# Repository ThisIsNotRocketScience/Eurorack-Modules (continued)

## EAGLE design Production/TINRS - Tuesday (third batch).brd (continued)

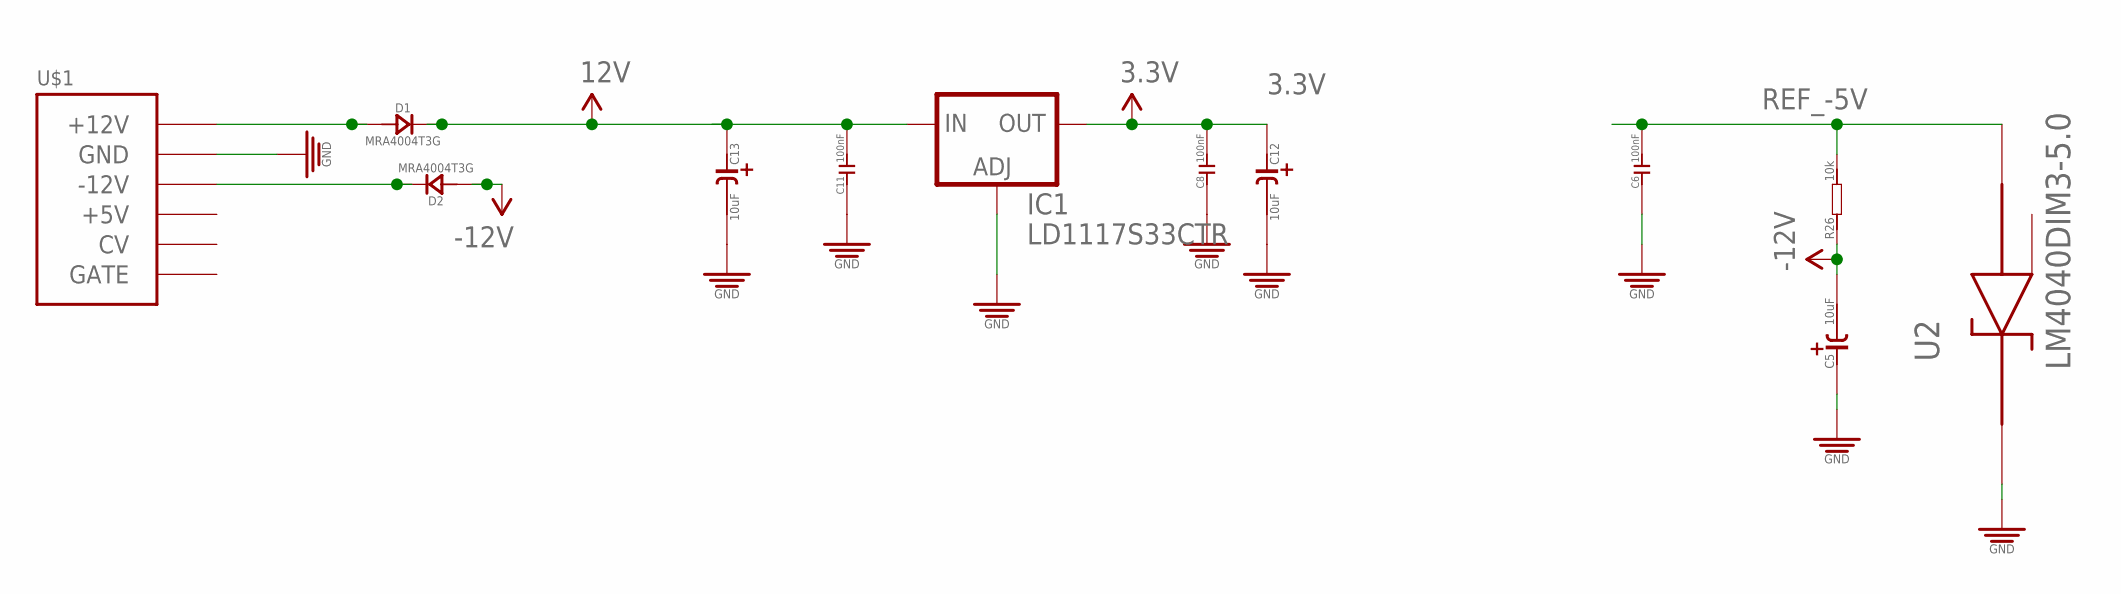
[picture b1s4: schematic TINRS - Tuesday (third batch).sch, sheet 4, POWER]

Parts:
C5, C12, C13: 10uF; CASE-A_3216; MPN TAJB106K020RNJ
C6: 100nF; C0603; MPN 06035C104KAT2A
C8, C11: 100nF; C0603; MPN MC0603F104Z160CT
D1, D2: MRA4004T3G; DO-214AC; MPN US1G-E3/5AT
IC1: LD1117S33CTR; SOT223; MPN LD1117AS33TR
R26: 10k; R0603
U2: LM4040DIM3-5.0; SOT95P237X112-3N
U$1: POWERSMT; 2X08_SMT_HEADER

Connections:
3.3V: C8.2, C12.+ (1), IC1.2 (OUT), IC1.4 (OUT); also elsewhere on the board
12V: C11.2, C13.+ (1), D1.2 (-), IC1.3 (IN); also elsewhere on the board
-12V: C5.- (2), D2.1 (+), R26.1; also elsewhere on the board
GND: C5.+ (1), C6.1, C8.1, C11.1, C12.- (2), C13.- (2), IC1.1 (ADJ), U2.1 (CATHODE), U$1.3 (GND), U$1.4 (GND), U$1.5 (GND), U$1.6 (GND), U$1.7 (GND), U$1.8 (GND); also elsewhere on the board
unnamed: D1.1 (+), U$1.9 (+12V), U$1.10 (+12V)
unnamed: D2.2 (-), U$1.1 (-12V), U$1.2 (-12V)
REF_-5V: C6.2, R26.2, U2.2 (ANODE); also elsewhere on the board

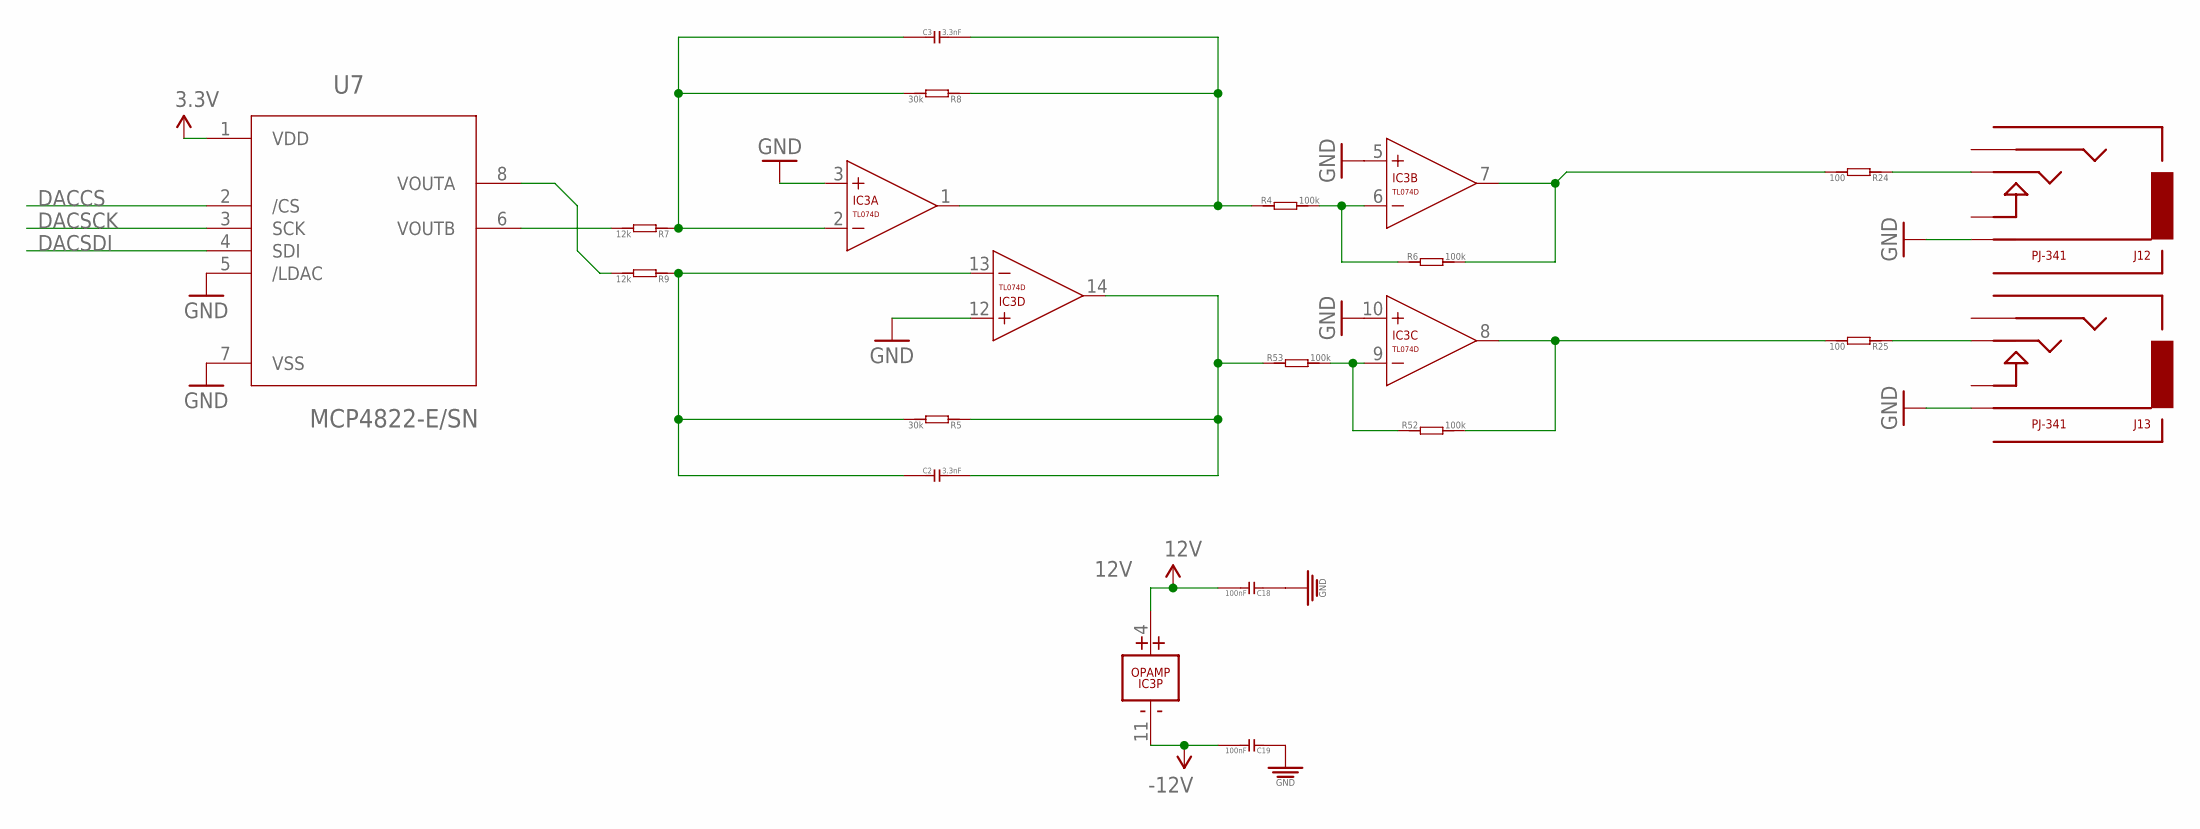
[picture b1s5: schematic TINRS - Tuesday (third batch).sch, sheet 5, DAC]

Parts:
C2, C3: 3.3nF; C0603
C18, C19: 100nF; C0603; MPN MC0603F104Z160CT
IC3: TL074D; SO14; MPN TL074CD
J12, J13: PJ-341; 3.5MM-JACK-SWITCH-13MM-OUTPUT
R4, R6, R52, R53: 100k; R0603
R5, R8: 30k; R0603
R7, R9: 12k; R0603
R24, R25: 100; R0603
U7: MCP4822-E/SN; SOIC8-N_MC

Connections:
3.3V: U7.1 (VDD); also elsewhere on the board
12V: C18.2, IC3.4 (V+); also elsewhere on the board
-12V: C19.2, IC3.11 (V-); also elsewhere on the board
DACCS: U7.2 (/CS); also elsewhere on the board
DACSCK: U7.3 (SCK); also elsewhere on the board
DACSDI: U7.4 (SDI); also elsewhere on the board
GND: C18.1, C19.1, IC3.3 (+IN), IC3.5 (+IN), IC3.10 (+IN), IC3.12 (+IN), J12.RING@3 (RING), J13.RING@3 (RING), U7.5 (/LDAC), U7.7 (VSS); also elsewhere on the board
unnamed: IC3.6 (-IN), R4.2, R6.1
unnamed: R9.2, U7.8 (VOUTA)
unnamed: R7.2, U7.6 (VOUTB)
unnamed: C2.1, IC3.13 (-IN), R5.2, R9.1
unnamed: C3.1, IC3.2 (-IN), R7.1, R8.2
unnamed: IC3.7 (OUT), R6.2, R24.2
unnamed: IC3.9 (-IN), R52.1, R53.2
unnamed: C3.2, IC3.1 (OUT), R4.1, R8.1
unnamed: J13.TIP@3 (TIP), R25.1
unnamed: J12.TIP@3 (TIP), R24.1
unnamed: C2.2, IC3.14 (OUT), R5.1, R53.1
unnamed: IC3.8 (OUT), R25.2, R52.2

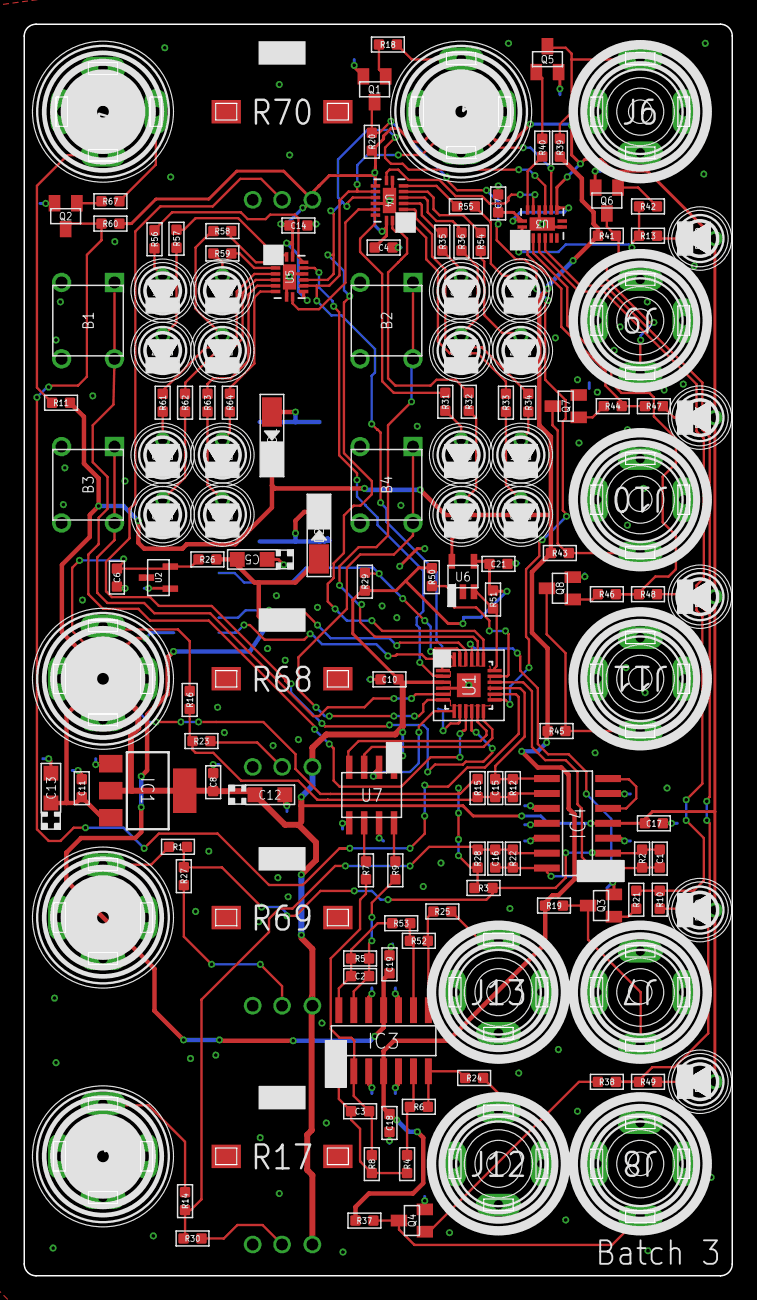
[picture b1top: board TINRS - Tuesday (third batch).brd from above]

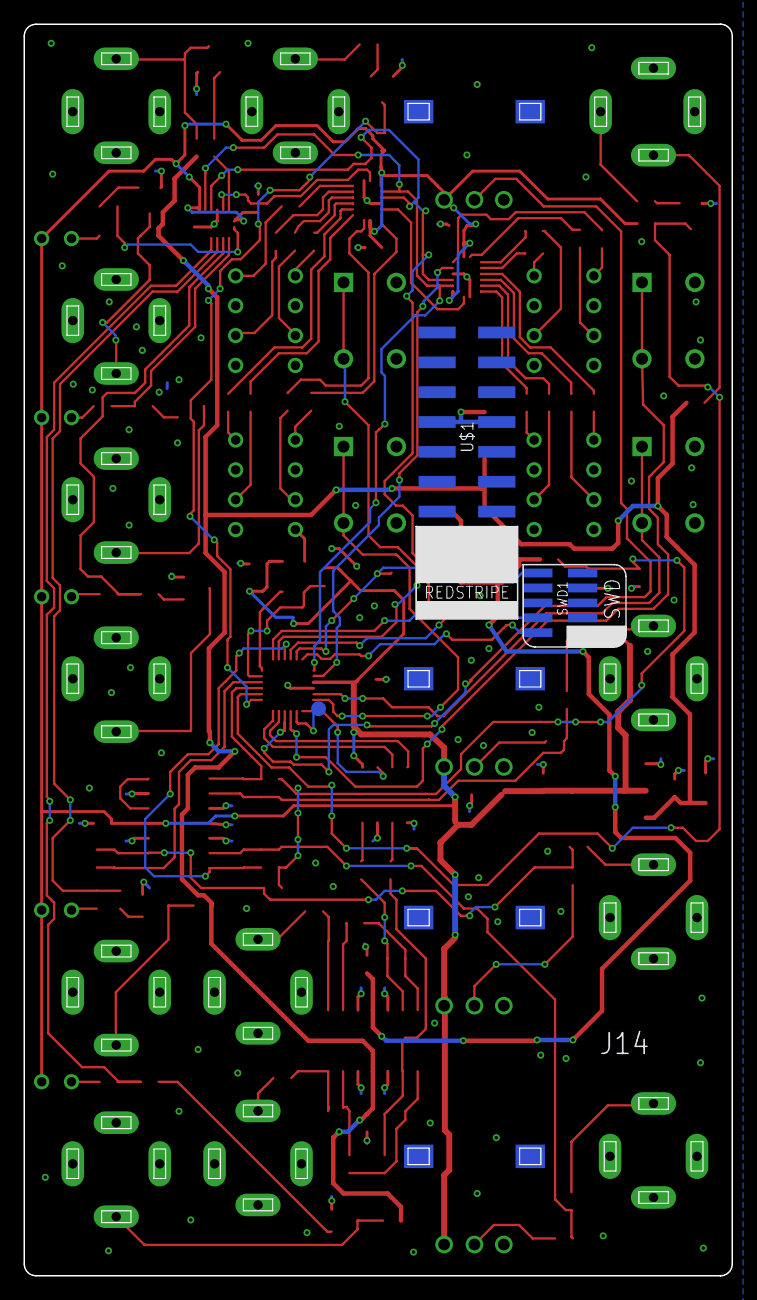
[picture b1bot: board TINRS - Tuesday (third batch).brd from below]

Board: 2 copper layers, 60.2 x 106.5 mm, 149 parts (3 on the bottom side), 113 nets.

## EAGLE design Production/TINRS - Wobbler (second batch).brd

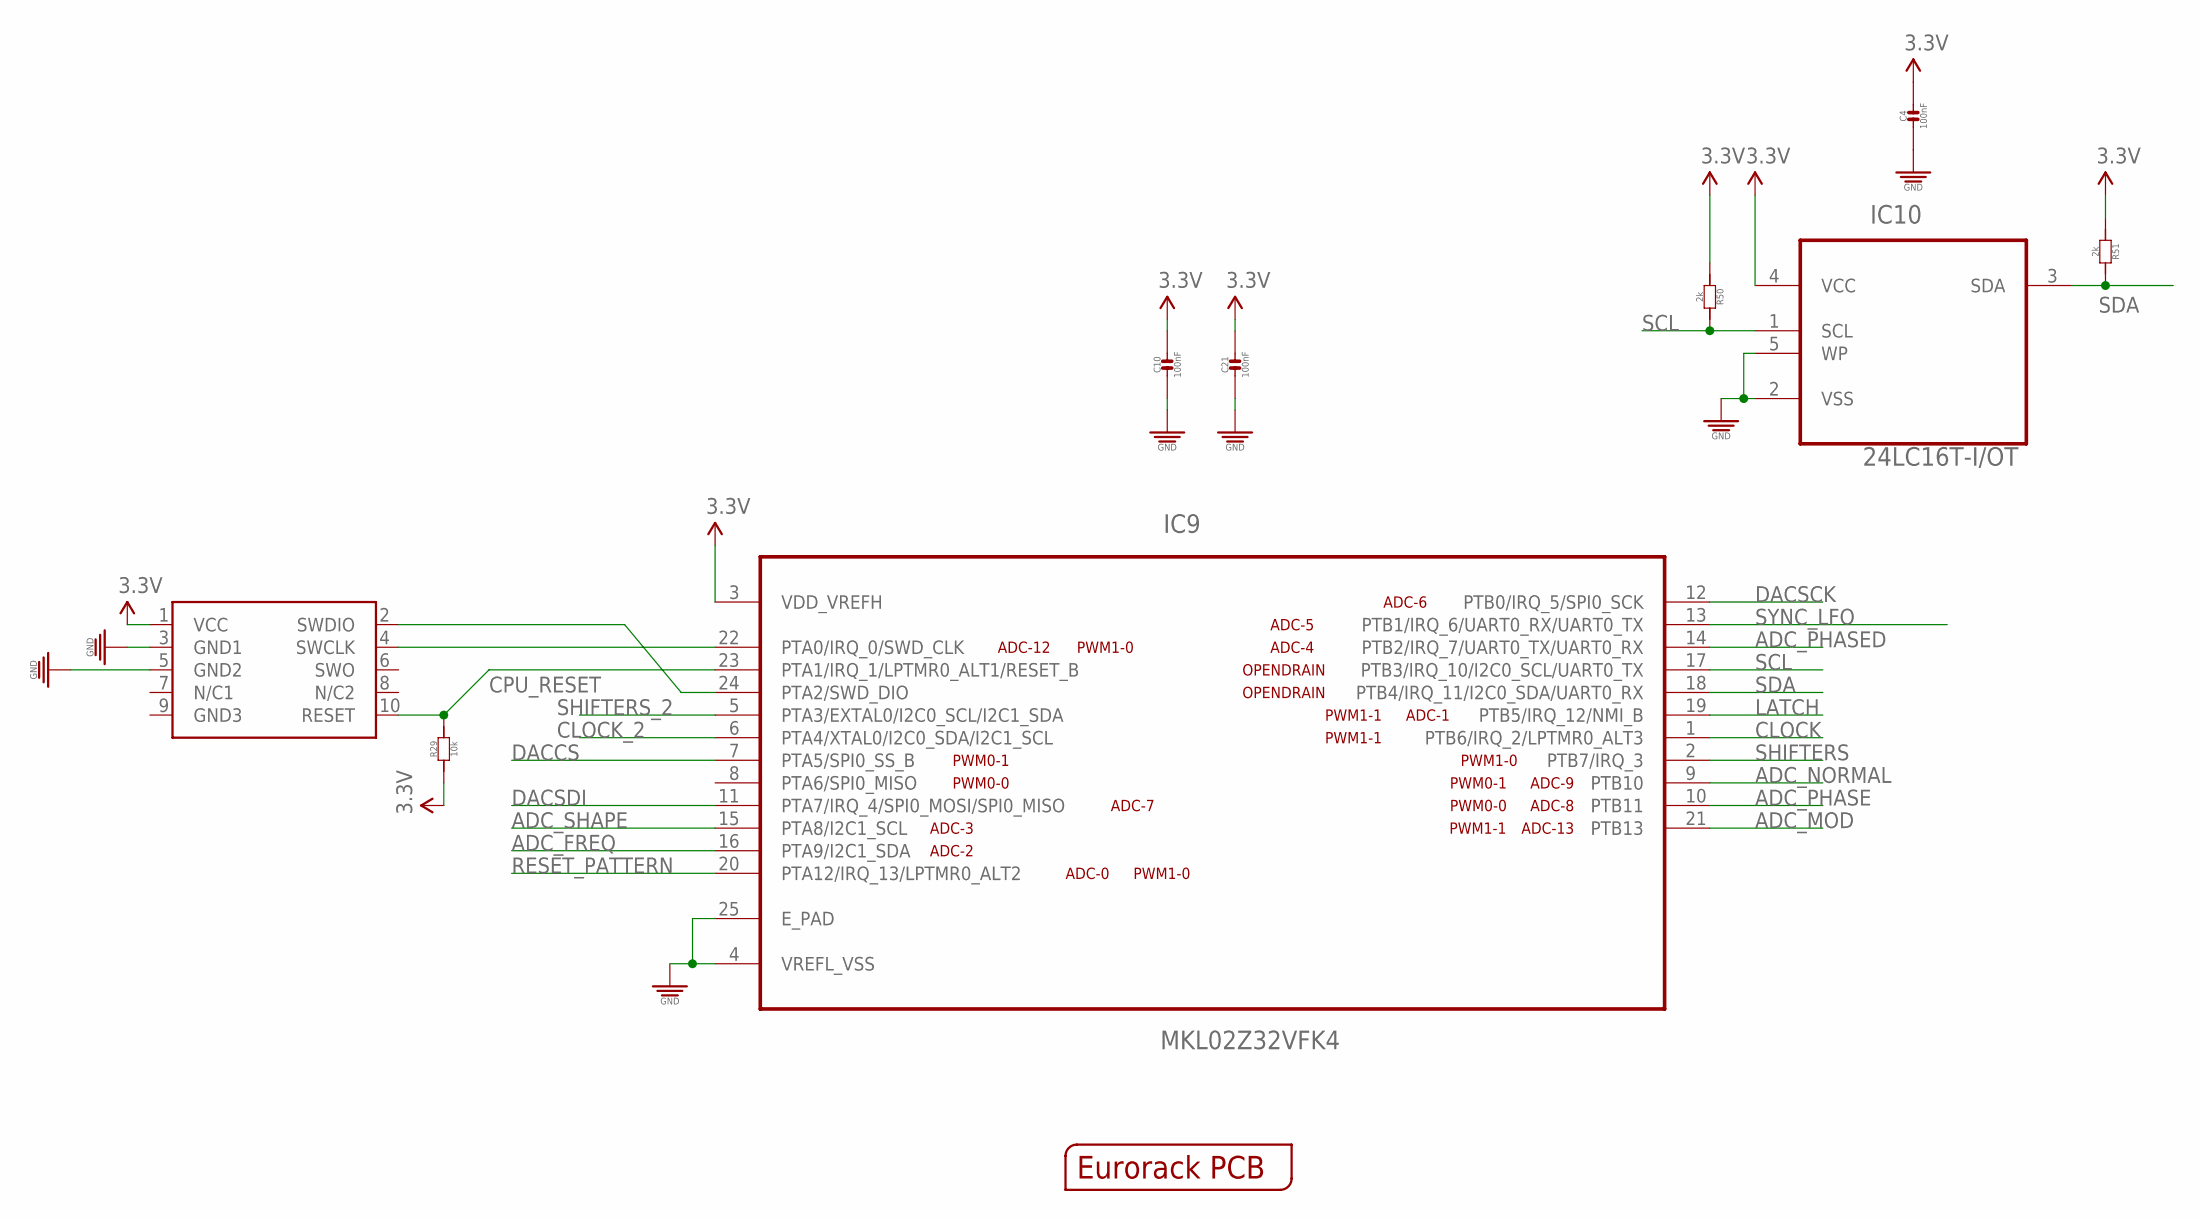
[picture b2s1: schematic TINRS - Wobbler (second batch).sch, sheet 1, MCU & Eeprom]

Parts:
C4, C10, C21: 100nF; C0603; MPN MC0603F104Z160CT
IC9: MKL02Z32VFK4; QFN50P400X400X100-25N
IC10: 24LC16T-I/OT; SOT95P290X145-5N; MPN 24LC00T-I/OT
OUTLINE: EURORACK_PCB12HP; EURORACK12HPPCB
R29: 10k; R0603
R50, R51: 2k; R0603
SWD1: CORTEX_SWD; M50-3600542

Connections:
3.3V: C4.2, C10.2, C21.2, IC9.3 (VDD_VREFH), IC10.4 (VCC), R29.1, R50.1, R51.1, SWD1.1 (VCC); also elsewhere on the board
ADC_FREQ: IC9.16 (PTA9/I2C1_SDA); also elsewhere on the board
ADC_MOD: IC9.21 (PTB13); also elsewhere on the board
ADC_NORMAL: IC9.9 (PTB10); also elsewhere on the board
ADC_PHASE: IC9.10 (PTB11); also elsewhere on the board
ADC_PHASED: IC9.14 (PTB2/IRQ_7/UART0_TX/UART0_RX); also elsewhere on the board
ADC_SHAPE: IC9.15 (PTA8/I2C1_SCL); also elsewhere on the board
CLOCK: IC9.1 (PTB6/IRQ_2/LPTMR0_ALT3); also elsewhere on the board
CLOCK_2: IC9.6 (PTA4/XTAL0/I2C0_SDA/I2C1_SCL); also elsewhere on the board
CPU_RESET: IC9.23 (PTA1/IRQ_1/LPTMR0_ALT1/RESET_B), R29.2, SWD1.10 (RESET)
DACCS: IC9.7 (PTA5/SPI0_SS_B); also elsewhere on the board
DACSCK: IC9.12 (PTB0/IRQ_5/SPI0_SCK); also elsewhere on the board
DACSDI: IC9.11 (PTA7/IRQ_4/SPI0_MOSI/SPI0_MISO); also elsewhere on the board
GND: C4.1, C10.1, C21.1, IC9.4 (VREFL_VSS), IC9.25 (E_PAD), IC10.2 (VSS), IC10.5 (WP), SWD1.3 (GND1), SWD1.5 (GND2); also elsewhere on the board
LATCH: IC9.19 (PTB5/IRQ_12/NMI_B); also elsewhere on the board
RESET_PATTERN: IC9.20 (PTA12/IRQ_13/LPTMR0_ALT2); also elsewhere on the board
SCL: IC9.17 (PTB3/IRQ_10/I2C0_SCL/UART0_TX), IC10.1 (SCL), R50.2
SDA: IC9.18 (PTB4/IRQ_11/I2C0_SDA/UART0_RX), IC10.3 (SDA), R51.2
SHIFTERS: IC9.2 (PTB7/IRQ_3); also elsewhere on the board
SHIFTERS_2: IC9.5 (PTA3/EXTAL0/I2C0_SCL/I2C1_SDA); also elsewhere on the board
SWD_CLK: IC9.22 (PTA0/IRQ_0/SWD_CLK), SWD1.4 (SWCLK)
SWD_DIO: IC9.24 (PTA2/SWD_DIO), SWD1.2 (SWDIO)
SYNC_LFO: IC9.13 (PTB1/IRQ_6/UART0_RX/UART0_TX); also elsewhere on the board

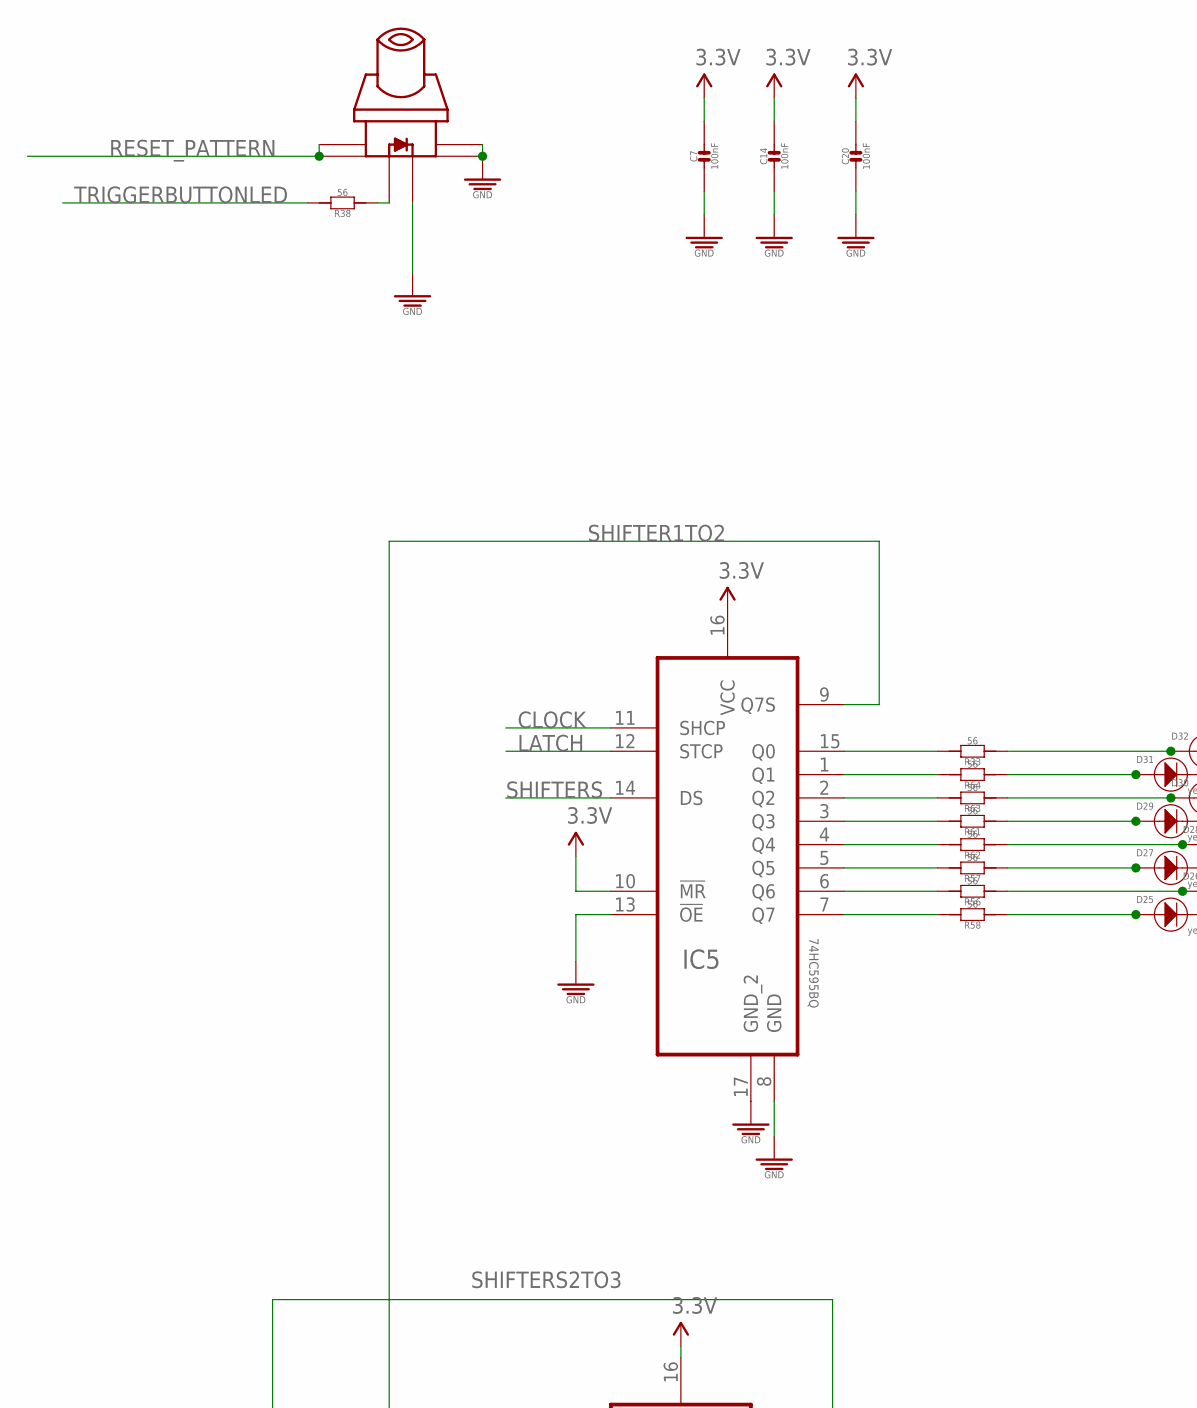
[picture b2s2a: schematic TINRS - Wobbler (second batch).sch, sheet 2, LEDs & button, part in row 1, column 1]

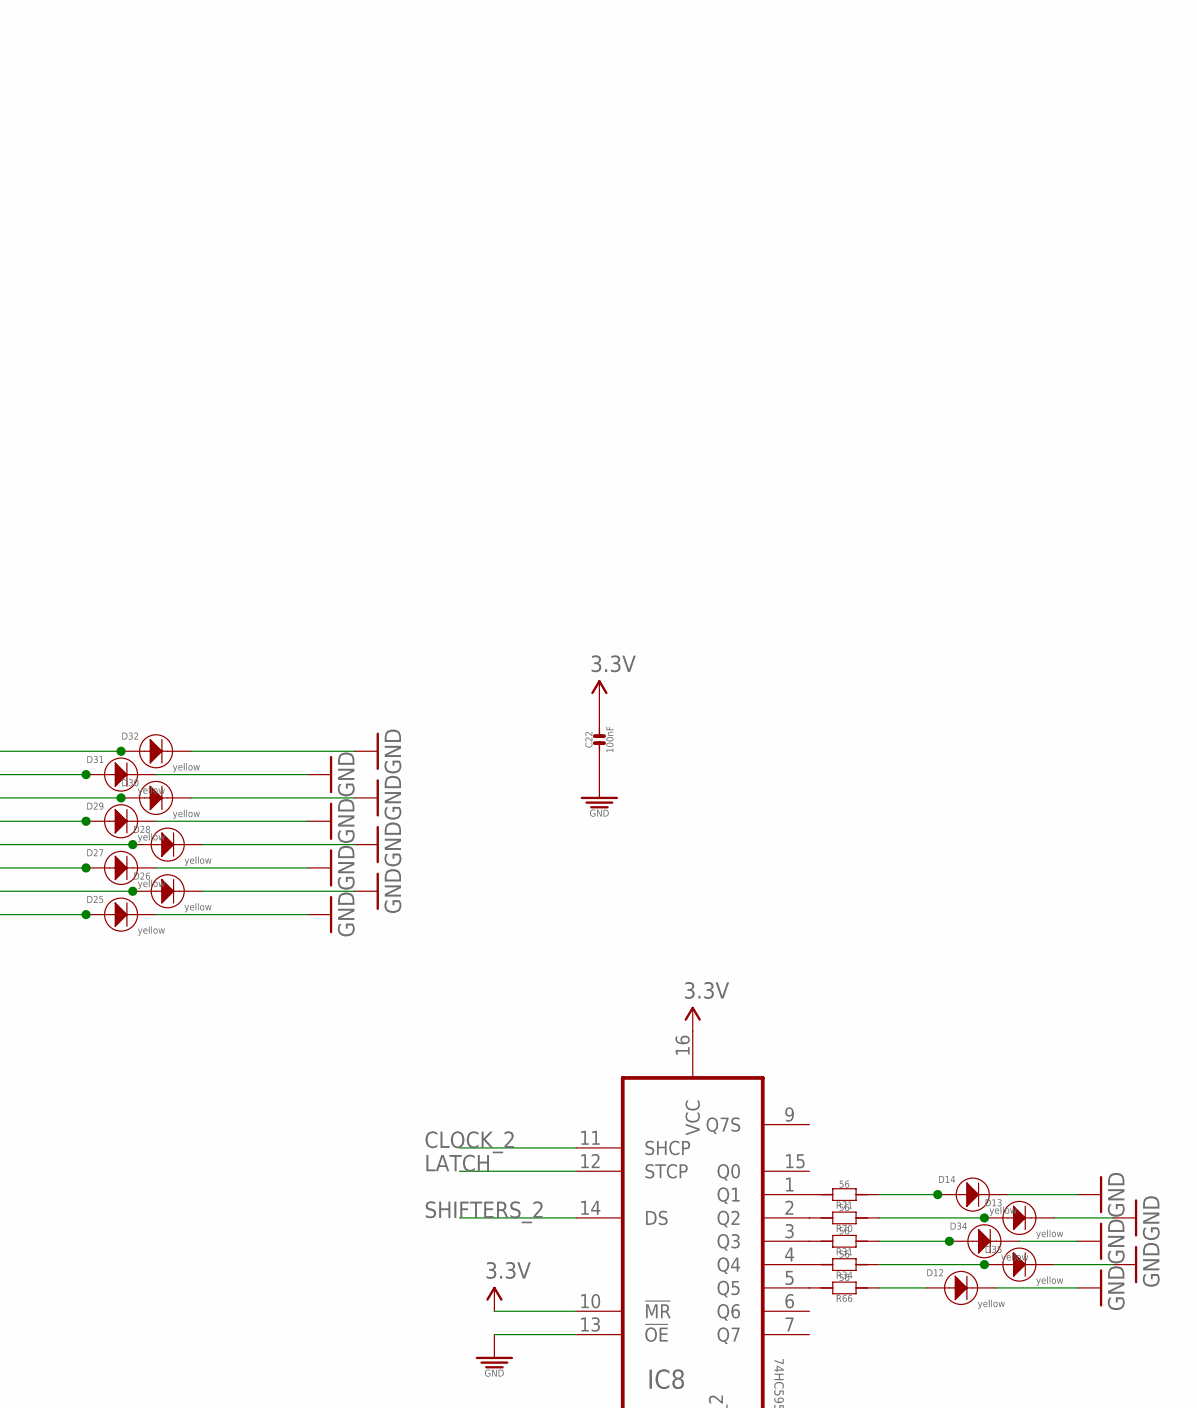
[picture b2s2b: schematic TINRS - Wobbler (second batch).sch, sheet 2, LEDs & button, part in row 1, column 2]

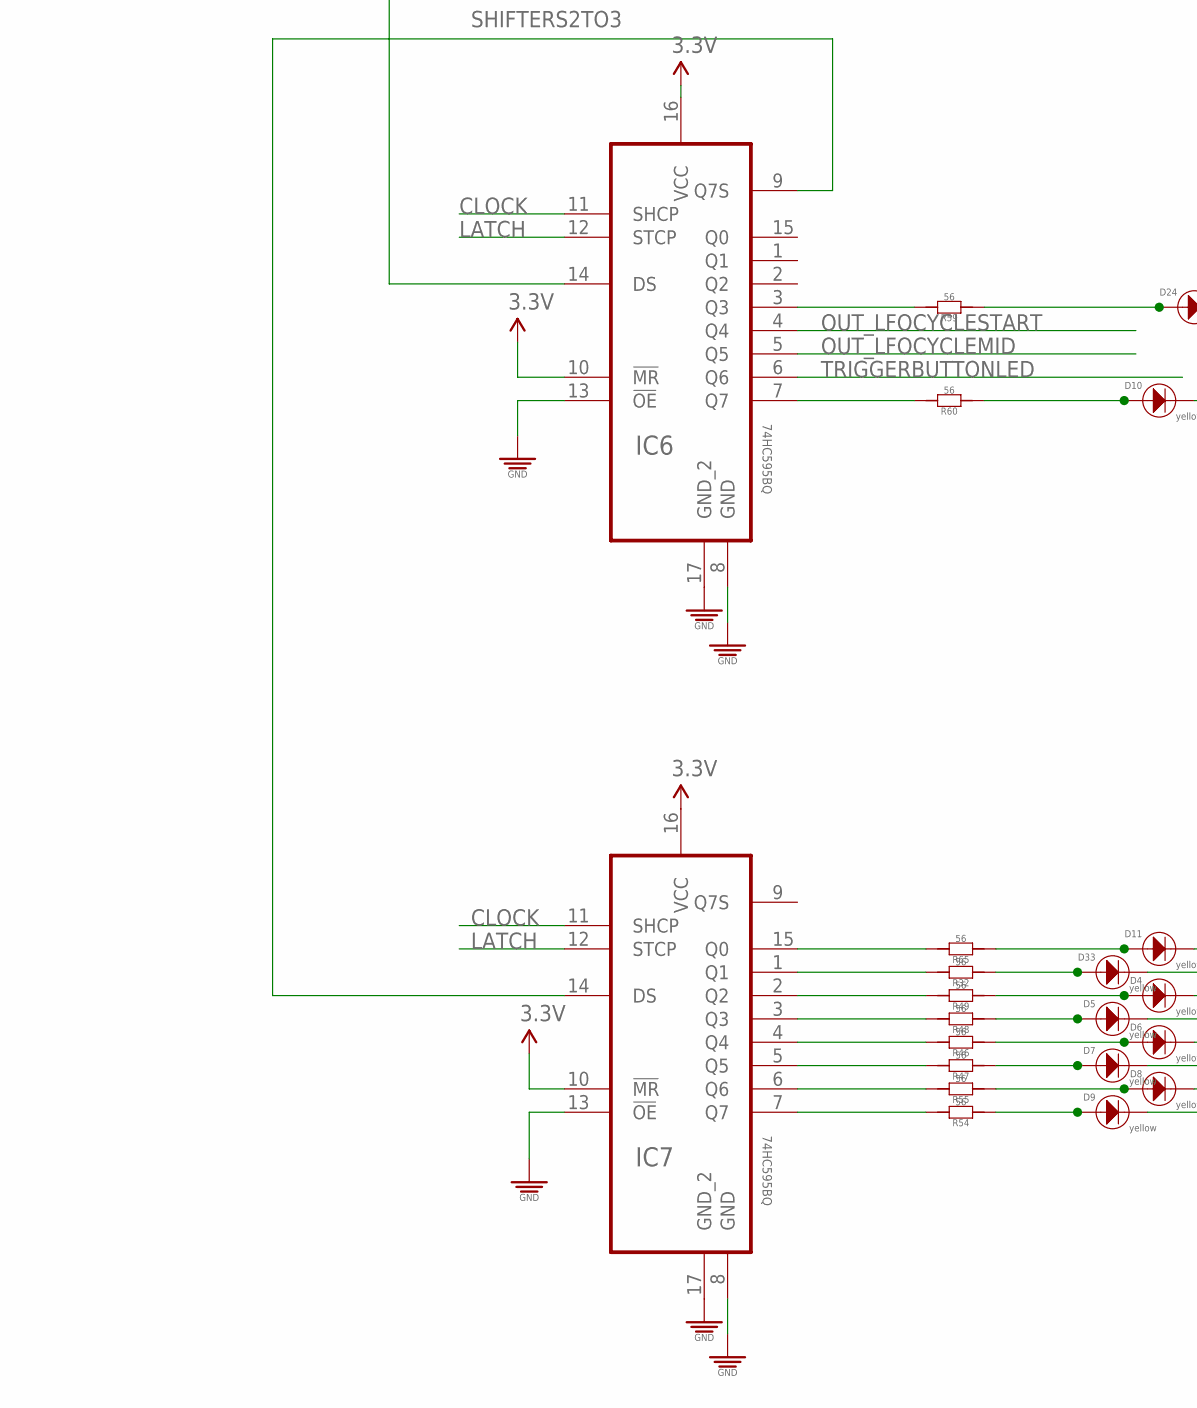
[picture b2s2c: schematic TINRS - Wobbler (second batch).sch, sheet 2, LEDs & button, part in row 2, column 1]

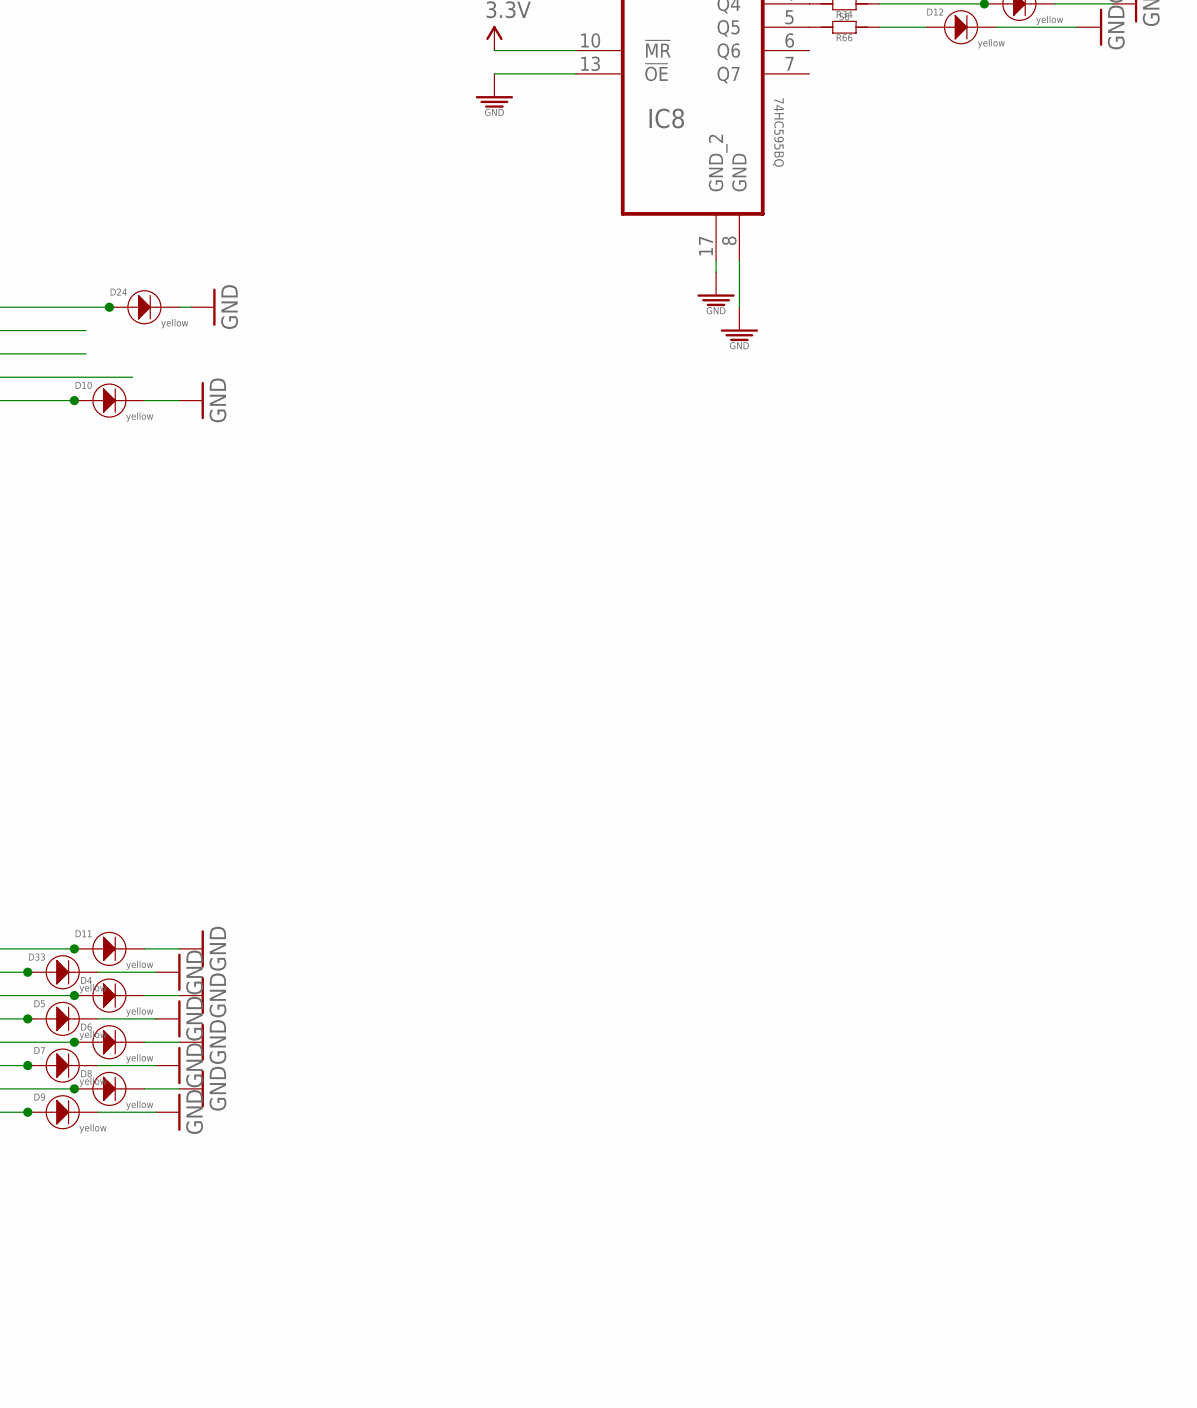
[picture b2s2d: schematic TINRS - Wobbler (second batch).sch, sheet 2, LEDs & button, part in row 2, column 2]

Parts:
C7, C14, C20, C22: 100nF; C0603; MPN MC0603F104Z160CT
D4, D5, D6, D7, D8, D9, D10, D11, D12, D13, D14, D24, D25, D26, D27, D28, D29, D30, D31, D32, D33, D34, D35: yellow; 3MMLED
IC5, IC6, IC7, IC8: 74HC595BQ; QFN50P250X350X100-17N
R31, R32, R33, R34, R38, R46, R47, R48, R49, R54, R55, R56, R57, R58, R59, R60, R61, R62, R63, R64, R65, R66, R70, R71: 56; R0603
U$1: SWITCH_W_LED_PB6149L-X-102YELLOW; PB6149L

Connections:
3.3V: C7.2, C14.2, C20.2, C22.2, IC5.10 (!MR), IC5.16 (VCC), IC6.10 (!MR), IC6.16 (VCC), IC7.10 (!MR), IC7.16 (VCC), IC8.10 (!MR), IC8.16 (VCC); also elsewhere on the board
CLOCK: IC5.11 (SHCP), IC6.11 (SHCP), IC7.11 (SHCP); also elsewhere on the board
CLOCK_2: IC8.11 (SHCP); also elsewhere on the board
GND: C7.1, C14.1, C20.1, C22.1, D4.-, D5.-, D6.-, D7.-, D8.-, D9.-, D10.-, D11.-, D12.-, D13.-, D14.-, D24.-, D25.-, D26.-, D27.-, D28.-, D29.-, D30.-, D31.-, D32.-, D33.-, D34.-, D35.-, IC5.8 (GND), IC5.13 (!OE), IC5.17 (GND_2), IC6.8 (GND), IC6.13 (!OE), IC6.17 (GND_2), IC7.8 (GND), IC7.13 (!OE), IC7.17 (GND_2), IC8.8 (GND), IC8.13 (!OE), IC8.17 (GND_2), U$1.3, U$1.4, U$1.LEDNEG (NEG); also elsewhere on the board
LATCH: IC5.12 (STCP), IC6.12 (STCP), IC7.12 (STCP), IC8.12 (STCP); also elsewhere on the board
unnamed: IC5.15 (Q0), R33.2
unnamed: D7.+, R47.1
unnamed: IC5.1 (Q1), R64.2
unnamed: IC5.2 (Q2), R63.2
unnamed: IC5.3 (Q3), R61.2
unnamed: D28.+, R62.1
unnamed: IC5.4 (Q4), R62.2
unnamed: IC5.5 (Q5), R57.2
unnamed: D29.+, R61.1
unnamed: IC5.6 (Q6), R56.2
unnamed: IC5.7 (Q7), R58.2
unnamed: IC6.3 (Q3), R59.2
unnamed: IC7.7 (Q7), R54.2
unnamed: IC7.6 (Q6), R55.2
unnamed: IC7.5 (Q5), R47.2
unnamed: R38.1, U$1.LEDPOS (POS)
unnamed: D13.+, R70.1
unnamed: IC7.4 (Q4), R46.2
unnamed: D6.+, R46.1
unnamed: D5.+, R48.1
unnamed: D4.+, R49.1
unnamed: D8.+, R55.1
unnamed: D9.+, R54.1
unnamed: D10.+, R60.1
unnamed: D11.+, R65.1
unnamed: IC7.3 (Q3), R48.2
unnamed: IC7.2 (Q2), R49.2
unnamed: IC7.1 (Q1), R32.2
unnamed: IC7.15 (Q0), R65.2
unnamed: IC6.7 (Q7), R60.2
unnamed: D14.+, R71.1
unnamed: IC8.1 (Q1), R71.2
unnamed: IC8.2 (Q2), R70.2
unnamed: D12.+, R66.1
unnamed: IC8.3 (Q3), R31.2
unnamed: IC8.4 (Q4), R34.2
unnamed: IC8.5 (Q5), R66.2
unnamed: D27.+, R57.1
unnamed: D26.+, R56.1
unnamed: D25.+, R58.1
unnamed: D24.+, R59.1
unnamed: D30.+, R63.1
unnamed: D31.+, R64.1
unnamed: D32.+, R33.1
unnamed: D33.+, R32.1
unnamed: D34.+, R31.1
unnamed: D35.+, R34.1
OUT_LFOCYCLEMID: IC6.5 (Q5); also elsewhere on the board
OUT_LFOCYCLESTART: IC6.4 (Q4); also elsewhere on the board
RESET_PATTERN: U$1.1, U$1.2; also elsewhere on the board
SHIFTER1TO2: IC5.9 (Q7S), IC6.14 (DS)
SHIFTERS: IC5.14 (DS); also elsewhere on the board
SHIFTERS2TO3: IC6.9 (Q7S), IC7.14 (DS)
SHIFTERS_2: IC8.14 (DS); also elsewhere on the board
TRIGGERBUTTONLED: IC6.6 (Q6), R38.2
